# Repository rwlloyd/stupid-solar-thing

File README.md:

# Stupid Solar Thing

**R. Lloyd**. Lincoln. June 2021.

Any field sensor needs to have a load of boilerplate hardware and firmware before we go hooking a sensor up to it. On the hardware side of things, starting with the power source and ending with the microcontroller, we need:

- Solar Panel
- Charge controller
- Battery
- Microcontroller

In the case of the first prototype, this:

- 2.5v Solar cell
- TP4056 Charge controller circuit
- Random Lipo battery that I'm hoping has enough capacity. It's small.
- Wemos D1 Mini (ESP8266 breakout)

Yeah, Wire that all together... I put a switch in for the Wemos. The output of the TP4056 going to the 5V and GND pins of the Wemos. Seemed appropriate. The Lipo is only chucking out ~4V at the moment, but the ESP is really a 3.3v device that is 5V tolerant (don't quote me on that, but I haven't fried one... yet).

Cool, so we're all done. Chuck a sensor on it and profit? 

Dont be soft in the head. The real key to this little gizmo is going to be the code on the ESP... (I'm calling the microcontroller that from now on because it's just struck me that this would work on an ESP32 based board too. I think).

So this code, what's going to be so magical and ground breaking about it? I hear you ask. Well, probably not much. I'm planning to ~~plagarise~~ fork most of it from other people and put it all together in a system taylored just for ~~me~~ us.

## Operation of the Thing.

Regardless of the sensor that we want to connect to the Thing. It's going to need to perform a few tasks. 

1. Wake up
2. Check the Battery
3. Check the Sensors
4. Save the data
5. Check the time
6. if time
    
    6.1 Connect to wifi

    6.2 Send Some data

7. Go into deep sleep

Now, It's tea time on a saturday. I'll be back in a bit.

---

I've had tea. now it's geekin time.

First things first, I've already made this circuit up. The ESP is curerently connected to wifi and the battery voltage is coming in at 4.5V... this is a bad thing. What's up with the charge controller? Im regretting checking the voltage already.

https://www.best-microcontroller-projects.com/tp4056.html

Ended up watching this next video and the not worrying about it as it's getting dark. The TP4056 has a protection circuit in it, so for now I'm just going to trust that it know's what it's doing and hope the lipo doesn't explode.

https://www.youtube.com/watch?v=dBx-g1dkdDQ

Moving on... That list up there. The first thing that strikes me is that it's incomplete. There are a few other niceties that I would like this device to have.

1. Over-the-air (OTA) updates. 
    - Not strictly necessary, but I can imagine deploying these things in relatively high numbers and I can't see updating them all manually being a fun job.

2. A small webserver that allows people on the same wifi network to log into the sensors directly. Maybe with some sort of passphrase/key used to modify settings.

Of these two items. We already have a webserver from last, bloody hell, months little project:

https://github.com/rwlloyd/p5-javascript-webserver

### Let's add OTA updates next...

OK, if you're into this stuff, Andreas Spiess on Youtube has excellent videos on subject around sensors and microcontrollers.

https://www.youtube.com/watch?v=1pwqS_NUG7Q&t=480s

Notes:

- If our sketch is OTA enabled, we can select a Network port in the arduino IDE rather than a serial port.

- The sketch has to have the OTA not the bootloader. literally, first 2 mins of the video.

Links in the description, but... https://github.com/SensorsIot/ESP32-OTA

### DHT22 Sensor

So that's that bit. Now, I got distracted thinking about how to connect an DHT22 temp/humidity sensor. It's three wires, non of that resistor stuff? I really need to read the datasheets for everything. They should look something like this:-

Excuse me while I just go and add that to the circuit. While I was at it, I also added a capacitive moisture sensor and changed the battery for a 18650 cell I pulled out of an old laptop battery ;). It now looks like this. Don't judge:

Noted should be that this is now on and running sketches.... It also has a different solar panel, because I dont think the 2.5V of the original one is enough to power the TP4056.

---

### Update: 22.59

It's still running sketches. But now it also connects to wifi and spits out sensor readings on the serial port. It also serves a p5.js sketch over http and... one minute while I check.... yep, that all seems to work fine. I've also changed the webserver to the ESP easy. 

Now, I'm getting sick of plugging in the usb. Gonna implement Over-The-Air (OTA) updates from:

https://github.com/SensorsIot/ESP32-OTA

Give me a minute....

Oh yes, this allows debugging over telnet too. So you need to install the 'TelnetStream' Library in the ArduinoIDE. Secondly, if you want to have the credentials for your network done automagically, here are the instructions from the github:

In order to use the code provided in this repository you need to provide the credentials of your access point. Or you can comment out the #include <credentials.h> and define the mySSID and myPASSWORD to the <setupOTA("TemplateSketch", mySSID, myPASSWORD) function.
Provide your credentials

Create a credentials.h file (in the sketch folder directly or in the Arduino library folder). For Windows, the library folder is located in the same folder as the sketch ([...]\Arduino\libraries\Credentials, [...]\Arduino).

The text file credentials.h looks like:

    #pragma once
    const char* mySSID = "SSID of your AP";
    const char* myPASSWORD = "Password of your AP";

## End of the day.

To Summarise. We now have a basic device that can

- Connect to Wifi
- Read Sensors
- Do OTA updates
- Display Debugging information over telnet

it can also 

- Serve webpages... But holy sheet is it a bit slow. Probably the libraries that im using. it took 51102ms to fetch the p5.min.js file of 484kb.

Theres also some stuff in there that I think will connect to a websocket, but that's for another day. Gonna leave everything running tonight and see how much the battery drains withough the solar cell.

### Next steps

Well, I guess it's back to that list at the top. But really the next things on my mind are:

- Displaying the sensor data in a p5js sketch
- Making websockets work
- Probably set up a crude webserver in node or maybe look into node-Red. We're going to have to start saving and graphing this data soon!

---

## Update 7/6/21

Hmm, well, I changed my mind. All this pissing around with websockets and fancy front ends and stuff is silly. Very fun and all that but silly. What we should really be doing is using..

### MQTT > node-red > influxDB > Grafana

I will apologise now for making any subsequent readers go through some of that stuff up there that wasn't relevant.

So, taking the sketch from last night, we're still using the OTA stuff and Telnet monitoring, but really, this thing needs to just communicate it's data as a JSON file over MQTT. We're going to need to manipulate the data on a computer anyway. So that's all done. Theres a new arduino sketch "stupid-solar-dht22-cmoist-mqtt.ino" - What? I like descriptive filenames for these things - that does just this. It check the sensors and then transmits them over wifi to the mqtt broker (I already had on Nyska). It all works. so really, I should build a node-red system for work and learn how to do graphana to make things look pretty. So that's what I'll probably do next.

Also, Future me, implement deep sleep on the ESP. Here's a guide to start with:

https://randomnerdtutorials.com/esp8266-deep-sleep-with-arduino-ide/

Basically,

1. Jumper between D0 and RST
2. Then you just add this when you want to run the deepsleep

        // Deep sleep mode for 30 seconds, 
        // the ESP8266 wakes up by itself when 
        // GPIO 16 (D0 in NodeMCU board) is connected to the RESET pin
        Serial.println("I'm awake, but I'm going into deep sleep mode for 30 seconds");
        ESP.deepSleep(30e6); 
        // Deep sleep mode until RESET pin 
        // is connected to a LOW signal (for example pushbutton or magnetic reed switch)
        //Serial.println("I'm awake, but I'm going into deep sleep mode until RESET pin is connected to a LOW signal");
        //ESP.deepSleep(0); 

If we're going the deepsleep route with the sensor, we might want to look at what's actually necessary for the sketch and trim things down a bit.... it is afterall going to be off most of the time. I think almost everything can be done in the setup. however, I think this will sacrifice OTA updates but we could do some fun things saving a load of data to RTC memory and only transmitting every 10 readings or something? Some more analogue pins would still be nice in the ESP too. However, I quite like the idea of multiplexing. So i think we could have another 5 yet. after 3 moist sensors a dht22 and a battery monitor?

## Update: 13/6/21

OK then, it's been a relatively busy few days and I've done a few things. 

1. I've been testing the prototype sensor. It's not bad but leaves a lot to be desired. Firstly it's chugging through too much power. This is mainly because I have it spewing out data every 2 seconds. So, we need to implement 

    - Longer Time period and deep sleep functionaity
    - Some way of reporting the battery voltage (hint, this makes things slightly complicated) 

2. Why do I want to have the voltage reported you ask? Mainly because there is now a nice way to visualise them! [GRAFANA](https://grafana.com/). I spent a morning setting it up at home. But a new server will need to be set up for future work elsewhere. The crux of it all was a blog post by [Jonathan Oxer at Superhouse](https://www.superhouse.tv/41-datalogging-with-mqtt-node-red-influxdb-and-grafana/). With that you will end up with a raspberry pi including:

    - Raspberry Pi OS
    - Mosquitto (MQTT Broker)
    - Node-RED
    - InfluxDB
    - Grafana

### Moving forward:

- Sort out Deep Sleep
- Work out a way to multiplex multiple analog devices with a single analog pin
- Add Light Dependent Resistor (LDR) to measure light levels
- Add Battery Voltage Measurement (start [here](https://randomnerdtutorials.com/esp8266-adc-reading-analog-values-with-nodemcu/) and [here](https://www.reddit.com/r/esp8266/comments/m4bkdc/how_to_get_battery_level_from_lolin_wemos_130/gquu8dr/))
- Make a schematic in Kicad
- Modify original prototype then build second prototype for field testing.

In the meantime, here are some pretty pictures.

### It's afternoon now... Let's think about multiplexing

Let's first think about the case where we are not measuring the battery voltage. Generally, simple analog sensors havce 3 pins. Power, GND and SIG. In basic terms, you give power to the sensor and whatever voltage you get at the SIG pin is your reading. In this case, all of the sensors are running at 3.3v and we will expect something below that for our output signal.

Unfortunately, the analog input of the ESP8266 Module will only tolerate 1V. Luckily, the makers of the Wemos, having envisioned this problem, put in a voltage divider so that 3.3V applied to the Wemos Analog in pin will show as 3.3v at the internal ESP analog pin. This is normally a voltage divider with a 100K resistor (R2) to ground, and a 220K resistor (R1) leading to the A0 pin. 

But our battery, when fully charged is 4.2v.... So to drop down the 4.2V to 3.3v, we need to use Ohms law to work out our resistor value...

    V = I x R
    4.2 - 3.3 = 0.9v .... don't be soft, I'm not typing all that out. 

Use a [Calculator](https://ohmslawcalculator.com/voltage-divider-calculator)

Cool, So we add a 110K resistor in series with the 4.2V coming from the battery. We won't max out the Analog pin and all is good with the world... But what about when we want to read something else with the analog pin? We need to be able to switch the wire to the battery... We'll need a switch that can be operated from the microcontroller. NO! Not a fucking relay! a little NPN transistor should do nicely something like this:

In this case, the battery is connected to the collector (1), a digital pin is connected to the base (2) and the emitter (3) is connected to the analog input. BOOM, a pin we can pull high or low to allow electric pixies to flow or not.

## Update 14/6/21

OK, so i did a load of faffing and apparently got most of the way to [this instructables post that explains it very well](https://www.instructables.com/Multiple-Analog-Inputs-on-Only-One-Analoge-Pin/)

So, hows about we get to multiplexing?!

Seriously, I'm just saving you time googling things...

https://www.programmingelectronics.com/arduino-millis-multiple-things/

https://learn.adafruit.com/multi-tasking-the-arduino-part-1/overview

I'm trying to do this with millis() and classes. But in the meantime, I bought some of these:

https://playground.arduino.cc/Learning/4051/

A whole £4 for 10 of them... it's ridiculous. I hope they work at 3.3v... Meh, they look useful anyway.

here's the datasheet for it:

[CD4051 Datasheet](/md-assets/cd4051b.pdf)

## Update 15/6/21
10.48 pm

^^^ I thought - "No" and went to bed.

it's now the 19th and the data looks like this:

Looking pretty good, but it hides a whole host of problems. Primarily that multiplexing the analog pins in software, while keeping track of timings - because you can't use blocking code - keeps breaking OTA updates and deep sleep and so, the CD4051BE (Analog Mutiplexer) chips have arrived and now we'll try using them. The look and work like the picture below

So, as you can see, theres a bitmask to select which input you're reading.... Yeah, possible to roll my own but that's not how programming works. Somone has done this before, so we should use thier code. Thankyou https://ajfisher.me/

~~And thankyou for this library https://github.com/ajfisher/arduino-analog-multiplexer ~~

Actually, scratch that, I've found a different library that will work for different chips (Futureproof?) and is availiable in the default arduino libraries. It's this one:

https://github.com/stechio/arduino-ad-mux-lib

In the add library dialogue in the arduino IDE, search: 

    ad-mux-lib

Then we need to look up how to hook it up using:

    Z ----- common input/output (connected to Arduino Input/Output)
    E ----- enable input (active LOW) (connected to ground (gnd))
    Vee --- negative supply voltage (connected to ground (gnd))
    gnd --- ground (0 V)
    S0-S2 - select inputs (connected to three arduino digitalOut Pins)
    y0-y7 - independent inputs/outputs
    Vcc --- positive supply voltage (5v) 

## Test Mux

Completed code in 

`stupid-solar-thing\inspiration\CD4951-MuxAnalogReadExample-better\`

This code allows you to hook a couple of analog sensors up to a single analog pin and spits them out over serial.

## Make New Prototype

We're staring to get a bit complex with the connections. Up until now I've been drawing schematics on bits of paper here and there but it's mostle been point-to-point soldering and heat shrink. This isn't very professional and is beginning to look like a ratsnest of wires. So, time for [KiCad](https://www.kicad.org/).

... One Hour Later...

It's going fine, but I need a footprint for the TP4056 module. Apparently I already have them for the other bits, so you're on your own there.

https://github.com/alltheworld/tp4056

... Another Half-hour Later....

So, I'm not going to include the tp4056 on the schematic yet for a few reasons.

1. Nobody knows who really makes it, so it's not ideal for production. HOwever the schematics for the module are readily available. For now, the heatshrunk modules will be fine and if we make a proper PCB later, we'll just bake the module into the PCB.
2. The pin footprints of the modules are weird, so it won't fit on a 0.1" spaced prototyping board anyway. 

With that in mind, the schematic is starting to look like this:

Starting top left we have:

- Transistor to turn the power to the sensors on and off (Otherwise we would be powering them all the time)
- DHT22 Temp and humidity sensor, connected to Wemos pin D5
- A resistor to drop the battery voltage below that tolerable by the Wemos/ESP analog pin (I think I discussed this earlier)
- A pin header for the capacitive moisture sensor
- A potential divider for the photoresistor

In the middle, the sensor connections to the Mux chip and wemos. As well as their connection to each other.... look at that lonely wire. I've also added the connection from Wemos D1 to RST this will allow for deep sleep. 

Also, yes, I've already spotted mistakes in the schematic above. But at this point, let's start building the pcb for funsies. Look, this is what greets you once you open the pcb editor

1hr to do the schematic, another hour to remember how the PCB routing software works, 30mins rejigging things to fit properly... Quick preview in the 3D viewer.... Ah, that's a bit of an oversight... Could I say it's a feature, not a bug?

## That's all very well and good. But I'm not being Stupid Enough!

While I was pondering the idiocy of putting the module in  an orientation that means I wont be able to program it in-situ. I realised that I'm making a stupid solar thing. that shouldnt have any sensors, it should just have the connecting points. Up until now I have been making something specific, a prototype, but I should be going even simpler. 

So if we stop at the multiplexer connected to the wemos, we will basically have something similar to an arduino uno with wifi. That will do me.

### Make The Plan

- Make a Wemos D1 mini breakout board that has a load of sensor inputs (via CD4051) that it can turn on and off via a transistor.
- Add a capacitor to the 5V/Battery input of the Wemos.
- Connect CD4051 to A0 and the three select lines.
- Add potential divider to measure battery voltage on 
- Breakout all other MUX inputs and unused Wemod digital outputs to 3 Pin headers. Include RX/TX with +ve and -ve?

Note: Like I said, I'm not being stupid enough. All the sensors will be dealt with with other stupid things.

### Do The Plan

Have I mentioned I hate doing PCB layouts?

I came across this from the arduino forums about 4051s... it seems that everyone has this sort of project in mind. Worth doing well then I guess!

https://forum.arduino.cc/t/4051-and-unused-pins/621019/8

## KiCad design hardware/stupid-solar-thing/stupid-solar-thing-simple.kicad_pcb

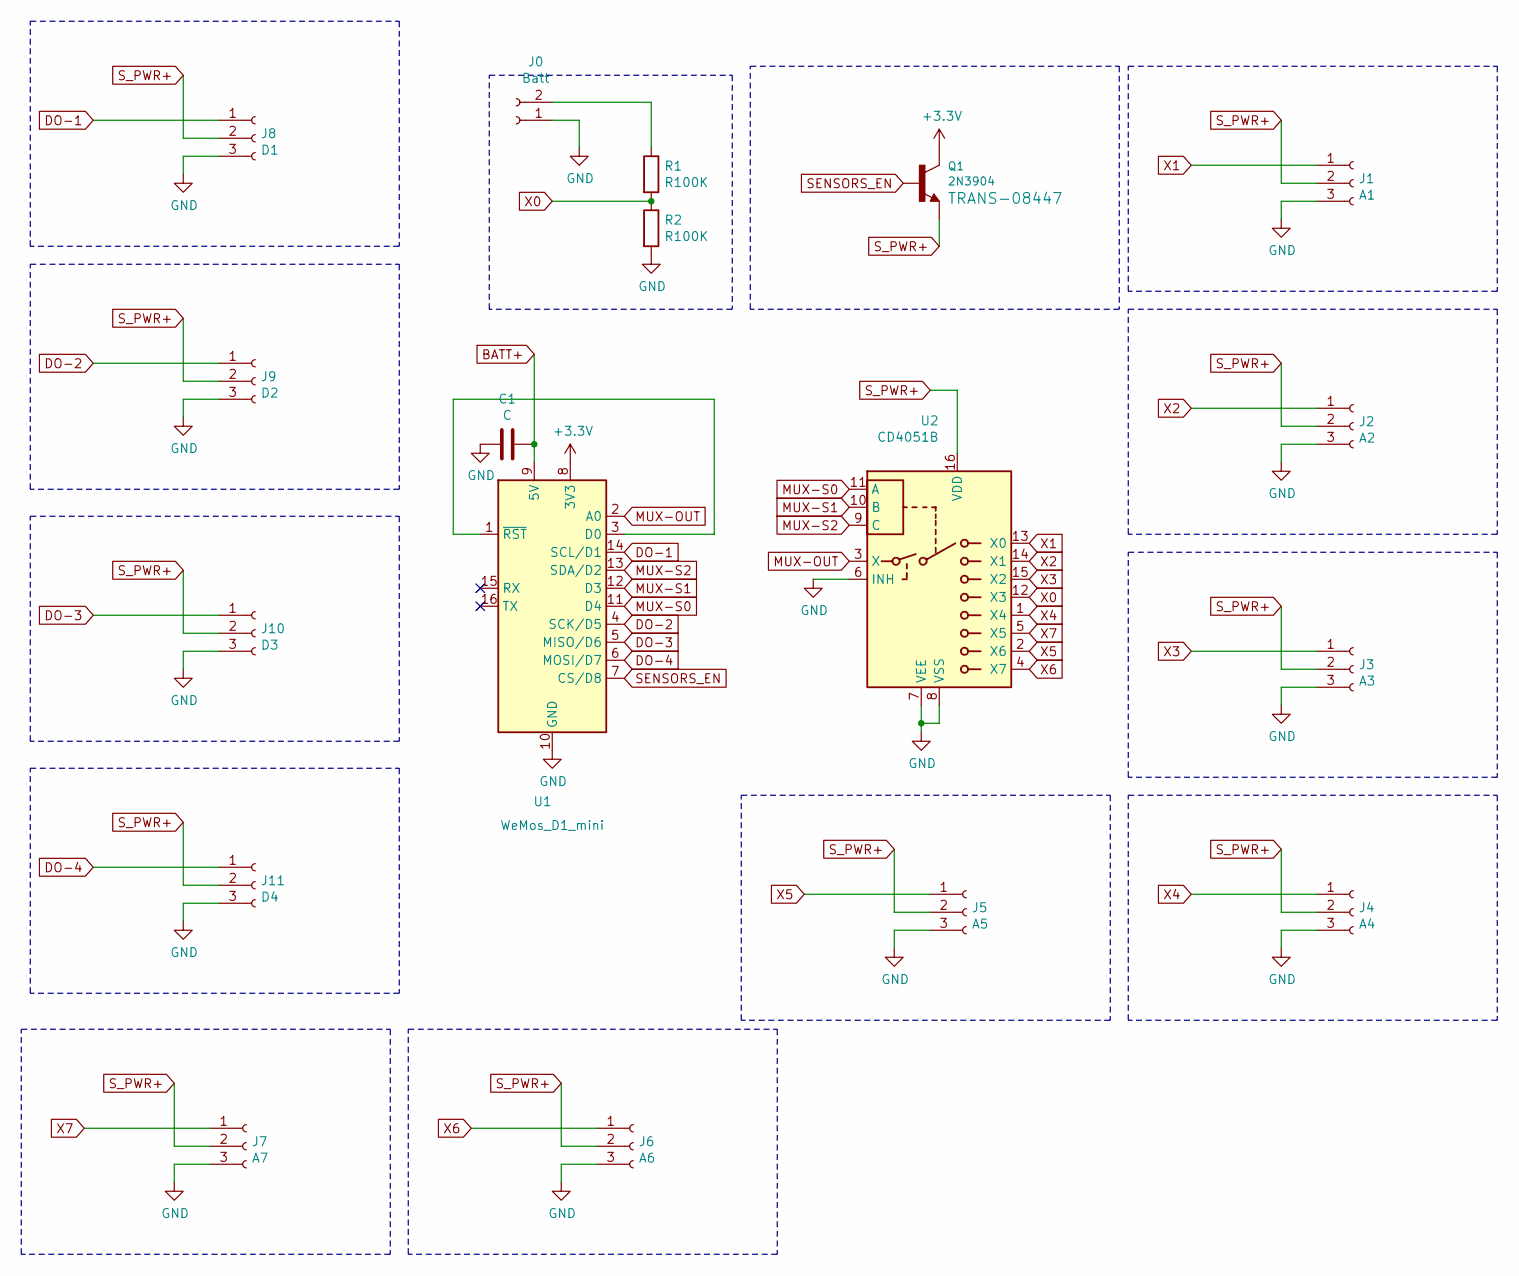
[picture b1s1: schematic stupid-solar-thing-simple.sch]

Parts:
C1: C; CP_Radial_D10.0mm_P5.00mm
J0: Batt; PinHeader_1x02_P2.54mm_Vertical
J1: A1; PinHeader_1x03_P2.54mm_Vertical
J2: A2; PinHeader_1x03_P2.54mm_Vertical
J3: A3; PinHeader_1x03_P2.54mm_Vertical
J4: A4; PinHeader_1x03_P2.54mm_Vertical
J5: A5; PinHeader_1x03_P2.54mm_Vertical
J6: A6; PinHeader_1x03_P2.54mm_Vertical
J7: A7; PinHeader_1x03_P2.54mm_Vertical
J8: D1; PinHeader_1x03_P2.54mm_Vertical
J9: D2; PinHeader_1x03_P2.54mm_Vertical
J10: D3; PinHeader_1x03_P2.54mm_Vertical
J11: D4; PinHeader_1x03_P2.54mm_Vertical
Q1: 2N3904; TO-92
R1, R2: R100K; R_Axial_DIN0207_L6.3mm_D2.5mm_P10.16mm_Horizontal
U1: WeMos_D1_mini; WEMOS_D1_mini_light
U2: CD4051B; DIP-16_W7.62mm_Socket

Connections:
+3V3: Q1.3 (C), U1.8 (3V3)
BATT+: C1.2, U1.9 (5V)
DO-1: J8.1, U1.14 (SCL/D1)
DO-2: J9.1, U1.4 (SCK/D5)
DO-3: J10.1, U1.5 (MISO/D6)
DO-4: J11.1, U1.6 (MOSI/D7)
GND: C1.1, J0.1, J1.3, J2.3, J3.3, J4.3, J5.3, J6.3, J7.3, J8.3, J9.3, J10.3, J11.3, R2.2, U1.10 (GND), U2.6 (INH), U2.7 (VEE), U2.8 (VSS)
MUX-OUT: U1.2 (A0), U2.3 (X)
MUX-S0: U1.11 (D4), U2.11 (A)
MUX-S1: U1.12 (D3), U2.10 (B)
MUX-S2: U1.13 (SDA/D2), U2.9 (C)
unnamed: J0.2, R1.1
unnamed: U1.1 (~RST), U1.3 (D0)
SENSORS_EN: Q1.2 (B), U1.7 (CS/D8)
S_PWR+: J1.2, J2.2, J3.2, J4.2, J5.2, J6.2, J7.2, J8.2, J9.2, J10.2, J11.2, Q1.1 (E), U2.16 (VDD)
X0: R1.2, R2.1, U2.12 (X3)
X1: J1.1, U2.13 (X0)
X2: J2.1, U2.14 (X1)
X3: J3.1, U2.15 (X2)
X4: J4.1, U2.1 (X4)
X5: J5.1, U2.2 (X6)
X6: J6.1, U2.4 (X7)
X7: J7.1, U2.5 (X5)

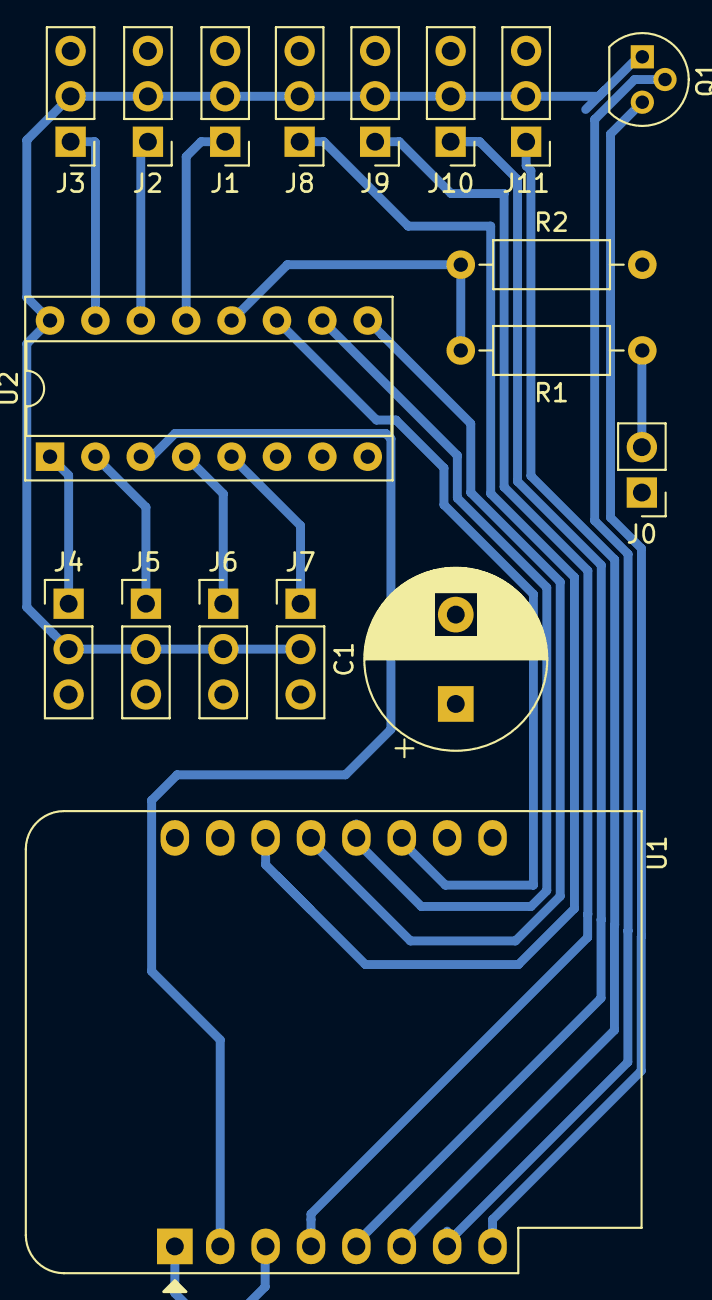
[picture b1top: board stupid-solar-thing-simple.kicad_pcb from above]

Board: 2 copper layers, 18 parts (0 on the bottom side), 23 nets.

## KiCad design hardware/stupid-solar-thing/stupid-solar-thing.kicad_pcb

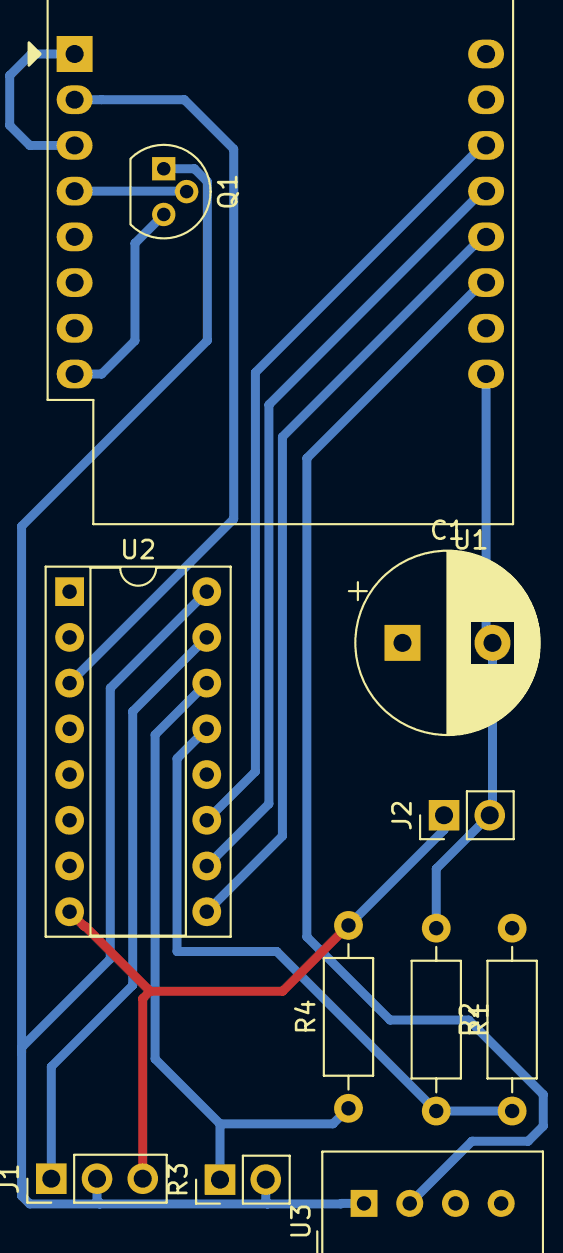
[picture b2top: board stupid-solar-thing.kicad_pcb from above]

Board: 2 copper layers, 11 parts (0 on the bottom side), 14 nets.

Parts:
C1: C; CP_Radial_D10.0mm_P5.00mm
J1: CM_SEN; PinHeader_1x03_P2.54mm_Vertical
J2: Batt; PinHeader_1x02_P2.54mm_Vertical
Q1: 2N3904; TO-92
R1, R2: R100K; R_Axial_DIN0207_L6.3mm_D2.5mm_P10.16mm_Horizontal
R3: R_PHOTO; PinHeader_1x02_P2.54mm_Vertical
R4: 10k; R_Axial_DIN0207_L6.3mm_D2.5mm_P10.16mm_Horizontal
U1: WeMos_D1_mini; WEMOS_D1_mini_light
U2: CD4051B; DIP-16_W7.62mm_Socket
U3: DHT11; Aosong_DHT11_5.5x12.0_P2.54mm

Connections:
+3V3: Q1.3, U1.8
BATT+: C1.2, J2.2, R1.1, U1.9
DHT22-SIG: U1.11, U3.2
GND: C1.1, J1.3, J2.1, R2.2, R4.2, U1.10, U2.6, U2.7, U2.8, U3.4
MUX-OUT: U1.2, U2.3
MUX-S0: U1.14, U2.11
MUX-S1: U1.13, U2.10
MUX-S2: U1.12, U2.9
unnamed: U1.1, U1.3
SENSORS_EN: Q1.2, U1.4
S_PWR+: J1.2, Q1.1, R3.2, U2.16, U3.1
X0: R1.2, R2.1, U2.13
X1: R3.1, R4.1, U2.14
X2: J1.1, U2.15

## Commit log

2021-06-21 Initial Proper Commit
